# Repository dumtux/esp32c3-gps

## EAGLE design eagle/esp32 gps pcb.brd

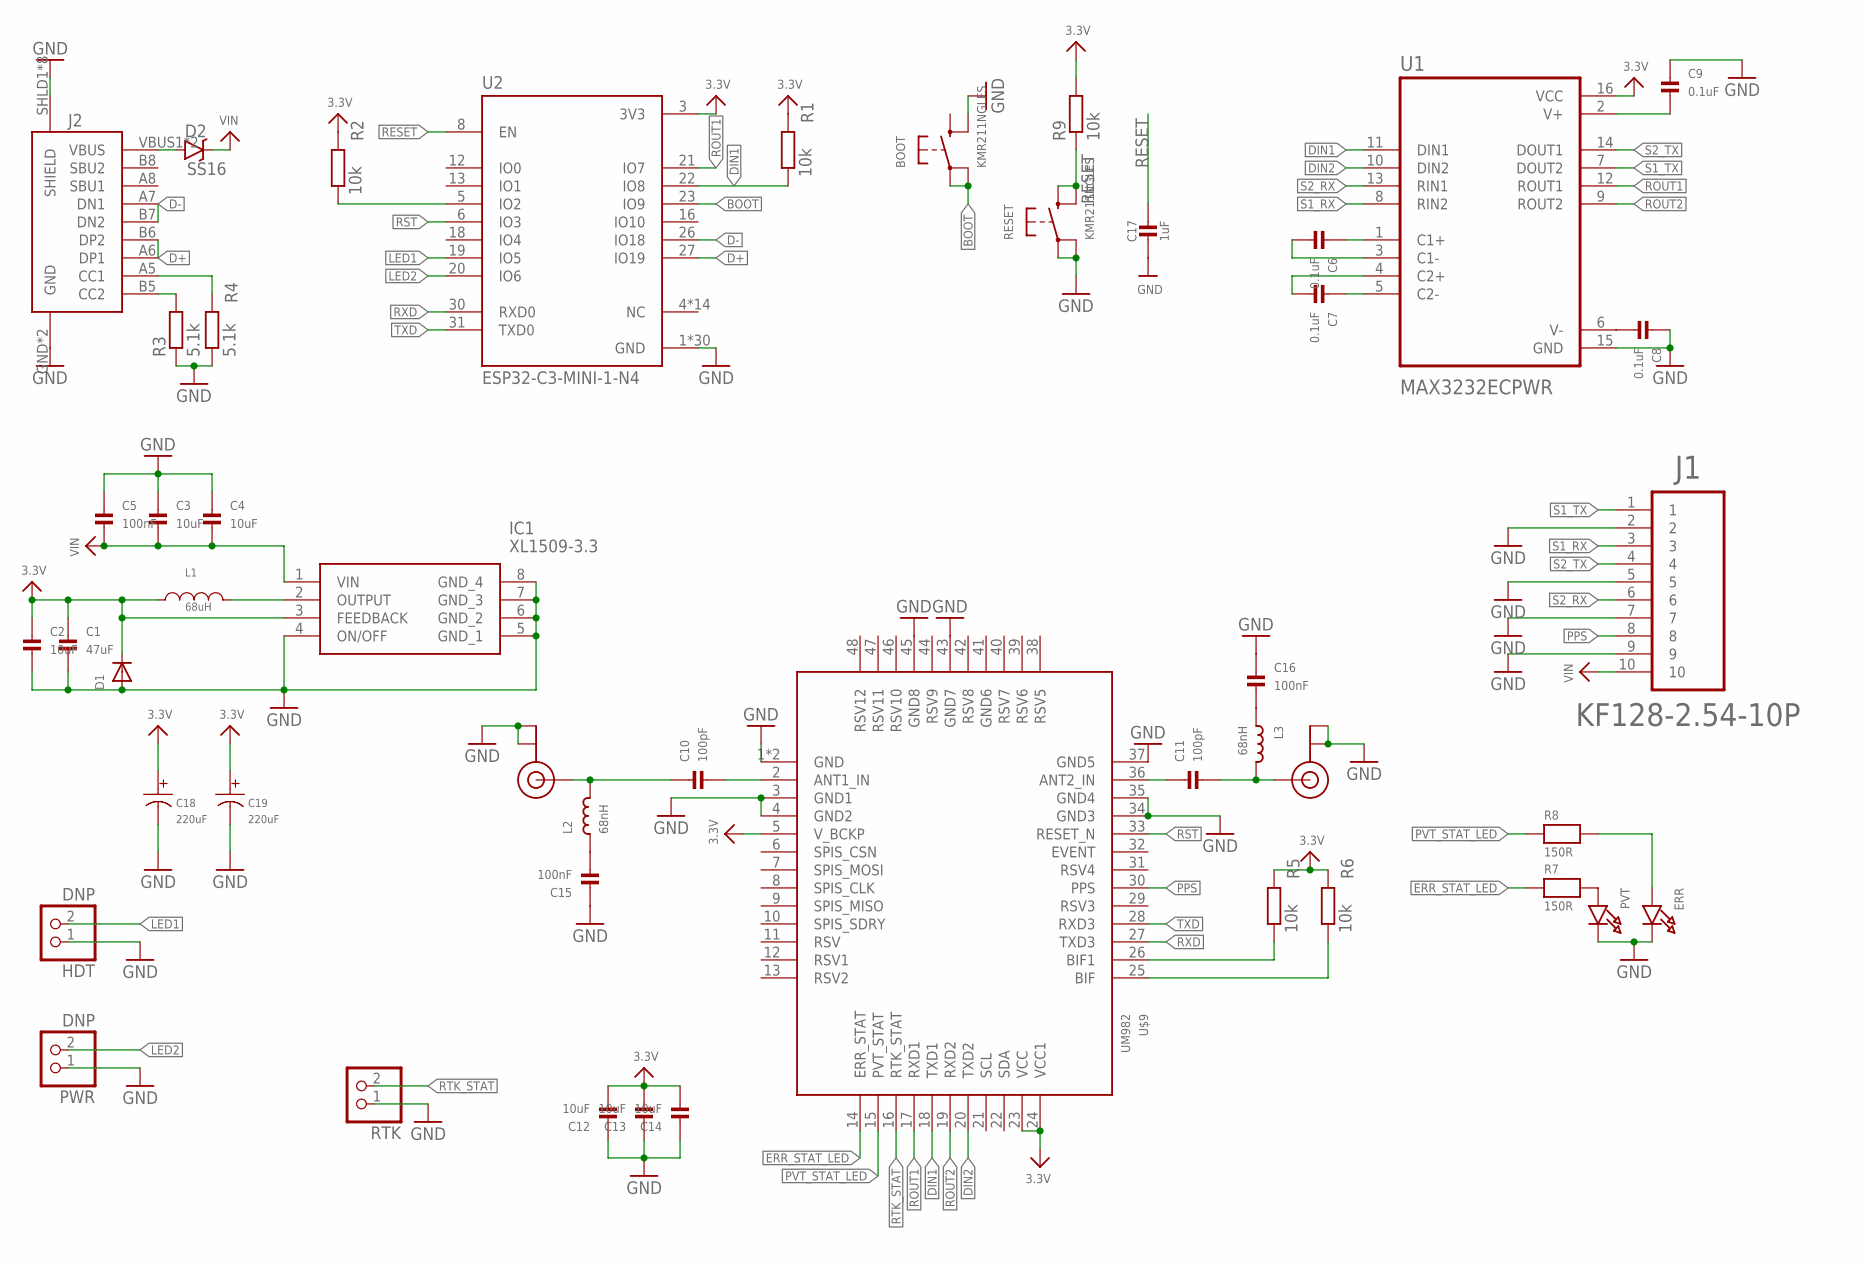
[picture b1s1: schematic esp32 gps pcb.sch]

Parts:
BOOT: KMR211NGLFS; BTN_KMR2_4.6X2.8
C1: 47uF; _0805
C2, C3, C4, C12, C13, C14: 10uF; _0603
C5, C15, C16: 100nF; _0603
C6, C7, C8, C9: 0.1uF; _0603
C10, C11: 100pF; _0603
C17: 1uF; _0603
C18, C19: 220uF; CAP-SMD_BD6.3-L6.6-W6.6-FD
D1: DIODESMA; SMADIODE
D2: SS16; SMA-DIODE
ERR: LED0603; CHIPLED_0603
HDT: DNP; 1X02_ROUND
IC1: XL1509-3.3; SOIC127P600X175-8N
J1: KF128-2.54-10P
J2: TYP-C16PIN2MD; USB-C-16P
L1: 68uH; IND-SMD_L6.0-W6.0
L2, L3: 68nH; _0603
PRI: KH-IPEX-K501-29; U.FL
PVT: LED0603; CHIPLED_0603
PWR: DNP; 1X02_ROUND
R1, R2, R5, R6: 10k; R0402
R3, R4: 5.1k; R0402
R7, R8: 150R; _0603
R9: 10k; R0603
RESET: KMR211NGLFS; BTN_KMR2_4.6X2.8
RTK: HEADER-1X2ROUND; 1X02_ROUND
SEC: KH-IPEX-K501-29; U.FL
U1: MAX3232ECPWR; SOP65P640X120-16N
U2: ESP32-C3-MINI-1-N4; XCVR_ESP32-C3-MINI-1-N4
U$9: UM982

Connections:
3.3V: C1.1, C2.1, C12.2, C13.2, C14.2, C18.1, C19.1, D1.C, IC1.3 (FEEDBACK), L1.1, R1.2, R2.2, R5.2, R6.2, R9.2, U1.16 (VCC), U2.3 (3V3), U$9.5 (V_BCKP), U$9.23 (VCC), U$9.24 (VCC1)
BOOT: BOOT.A, BOOT.A' (P1), U2.23 (IO9)
D+: J2.A6 (DP1), J2.B6 (DP2), U2.27 (IO19)
D-: J2.A7 (DN1), J2.B7 (DN2), U2.26 (IO18)
DIN1: R1.1, U1.11 (DIN1), U2.22 (IO8), U$9.18 (TXD1)
DIN2: U1.10 (DIN2), U$9.20 (TXD2)
ERR_STAT_LED: R7.1, U$9.14 (ERR_STAT)
GND: BOOT.B' (S1), C1.2, C2.2, C3.1, C4.1, C5.1, C8.1, C9.1, C12.1, C13.1, C14.1, C15.1, C16.1, C17.2, C18.2, C19.2, D1.A, ERR.C, HDT.1, IC1.4 (ON/OFF), IC1.5 (GND_1), IC1.6 (GND_2), IC1.7 (GND_3), IC1.8 (GND_4), J1.2, J1.5, J1.7, J1.9, J2.GND, J2.GND2 (GND), J2.SHLD1 (SHIELD), J2.SHLD2 (SHIELD), J2.SHLD3 (SHIELD), J2.SHLD4 (SHIELD), J2.SHLD5 (SHIELD), J2.SHLD6 (SHIELD), J2.SHLD7 (SHIELD), J2.SHLD8 (SHIELD), PRI.1 (GND), PRI.2 (GND), PVT.C, PWR.1, R3.1, R4.1, RESET.A, RESET.A' (P1), RTK.1, SEC.1 (GND), SEC.2 (GND), U1.15 (GND), U2.1 (GND), U2.2 (GND), U2.11 (GND), U2.14 (GND), U2.36 (GND), U2.37 (GND), U2.38 (GND), U2.39 (GND), U2.40 (GND), U2.41 (GND), U2.42 (GND), U2.43 (GND), U2.44 (GND), U2.45 (GND), U2.46 (GND), U2.47 (GND), U2.48 (GND), U2.49_1 (GND), U2.49_2 (GND), U2.49_3 (GND), U2.49_4 (GND), U2.49_5 (GND), U2.49_6 (GND), U2.49_7 (GND), U2.49_8 (GND), U2.49_9 (GND), U2.50 (GND), U2.51 (GND), U2.52 (GND), U2.53 (GND), U$9.1 (GND), U$9.3 (GND1), U$9.4 (GND2), U$9.34 (GND3), U$9.35 (GND4), U$9.37 (GND5), U$9.43 (GND7), U$9.45 (GND8), U$9.P$1 (GND)
LED1: HDT.2, U2.19 (IO5)
LED2: PWR.2, U2.20 (IO6)
unnamed: C6.1, U1.1 (C1+)
unnamed: C8.2, U1.6 (V-)
unnamed: C10.1, L2.2, PRI.3 (SIGNAL)
unnamed: C6.2, U1.3 (C1-)
unnamed: C9.2, U1.2 (V+)
unnamed: C10.2, U$9.2 (ANT1_IN)
unnamed: C7.1, U1.5 (C2-)
unnamed: C7.2, U1.4 (C2+)
unnamed: C11.1, U$9.36 (ANT2_IN)
unnamed: R5.1, U$9.26 (BIF1)
unnamed: J2.B5 (CC2), R3.2
unnamed: J2.A5 (CC1), R4.2
unnamed: D2.A, J2.VBUS1 (VBUS), J2.VBUS2 (VBUS)
unnamed: IC1.2 (OUTPUT), L1.2
unnamed: R2.1, U2.5 (IO2)
unnamed: R6.1, U$9.25 (BIF)
unnamed: C11.2, L3.2, SEC.3 (SIGNAL)
unnamed: C15.2, L2.1
unnamed: PVT.A, R7.2
unnamed: C16.2, L3.1
unnamed: ERR.A, R8.2
PPS: J1.8, U$9.30 (PPS)
PVT_STAT_LED: R8.1, U$9.15 (PVT_STAT)
RESET: C17.1, R9.1, RESET.B (S), RESET.B' (S1), U2.8 (EN)
ROUT1: U1.12 (ROUT1), U2.21 (IO7), U$9.17 (RXD1)
ROUT2: U1.9 (ROUT2), U$9.19 (RXD2)
RST: U2.6 (IO3), U$9.33 (RESET_N)
RTK_STAT: RTK.2, U$9.16 (RTK_STAT)
RXD: U2.30 (RXD0), U$9.27 (TXD3)
S1_RX: J1.3, U1.8 (RIN2)
S1_TX: J1.1, U1.7 (DOUT2)
S2_RX: J1.6, U1.13 (RIN1)
S2_TX: J1.4, U1.14 (DOUT1)
TXD: U2.31 (TXD0), U$9.28 (RXD3)
VIN: C3.2, C4.2, C5.2, D2.C, IC1.1 (VIN), J1.10

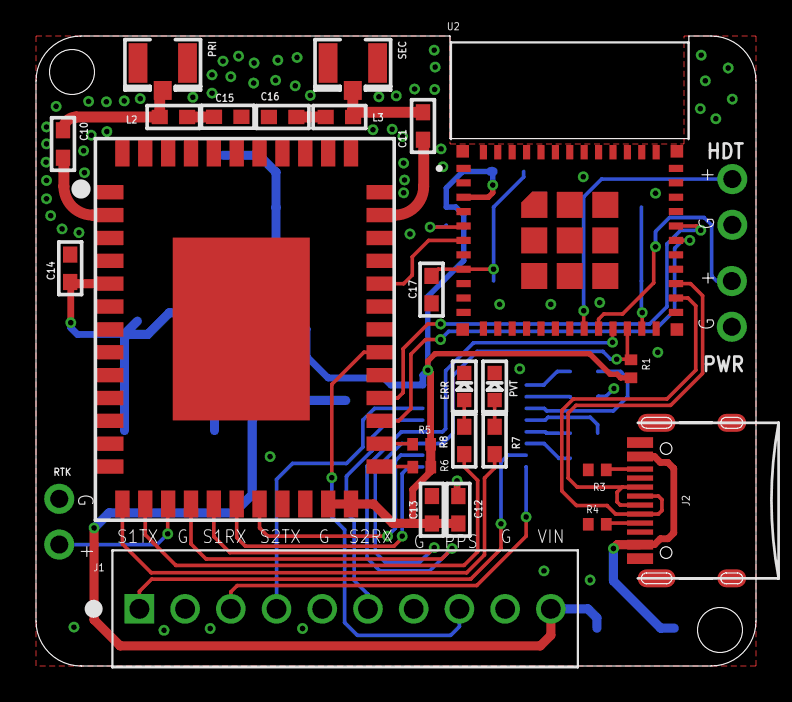
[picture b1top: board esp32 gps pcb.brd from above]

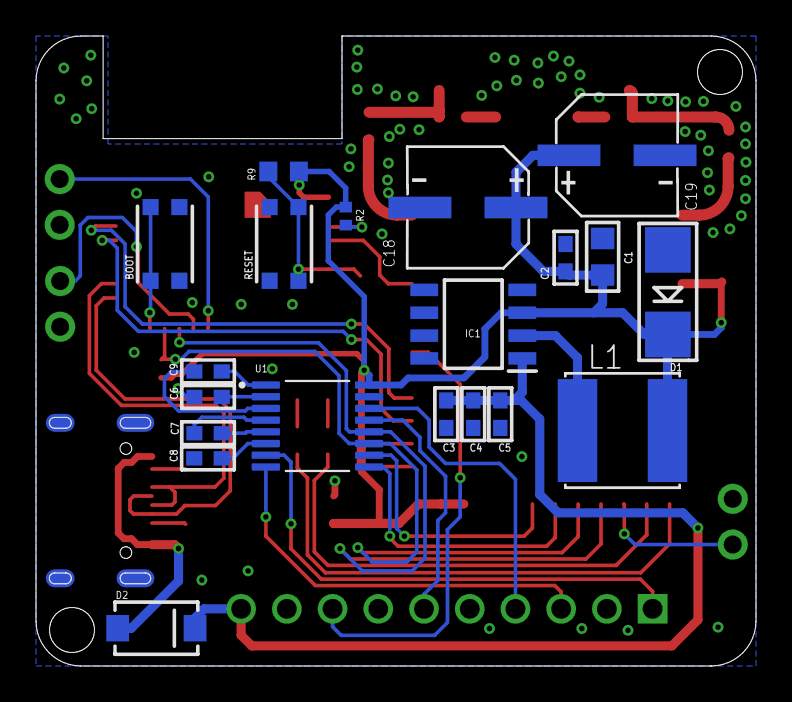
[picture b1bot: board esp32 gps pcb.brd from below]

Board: 2 copper layers, 40.0 x 35.0 mm, 48 parts (20 on the bottom side), 45 nets.

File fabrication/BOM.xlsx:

Qty | Value | Device | Package | Parts | Description | Manufacturer Part Number | LCSC Part Number
1 | SS16 | DIODESMA | SMADIODE | D1 | Diode
1 | Do not place | HEADER-1X2ROUND | 1X02_ROUND | RTK | PIN HEADER
2 | RED | LED0603 | CHIPLED_0603 | ERR, PVT | LED
1 | 68uH | PNLS6045-680 | PNLS6045-680 | L1 | 1.6A 68uH ±20% 330mΩ SMD,6x6x4.5mm Power Inductors ROHS | PNLS6045-680 | C2849542
1 |  | TYP-C16PIN2MD | USB-C-16P | J2 | Check availability
4 | 0.1uF | CAP_CERAMIC_0603 | _0603 | C6, C7, C8, C9 | Ceramic Capacitors
3 | 100nF | CAP_CERAMIC_0603 | _0603 | C5, C15, C16 | Ceramic Capacitors
2 | 100pF | CAP_CERAMIC_0603 | _0603 | C10, C11 | Ceramic Capacitors
4 | 10k | R-EU_R0402 | R0402 | R1, R2, R5, R6 | RESISTOR, European symbol
1 | 10k | R-EU_R0603 | R0603 | R9 | RESISTOR, European symbol
6 | 10uF | CAP_CERAMIC_0603 | _0603 | C2, C3, C4, C12, C13, C14 | Ceramic Capacitors
2 | 150R | RESISTOR_0603 | _0603 | R7, R8 | Resistors
1 | 1uF | CAP_CERAMIC_0603 | _0603 | C17 | Ceramic Capacitors
1 | 47uF | CAP_CERAMIC_0805 | _0805 | C1 | Ceramic Capacitors
2 | 220uF | CAP_Electrolytic | SMD,D6.3xL5.4mm | C18, C19 | Aluminum Electrolytic Capacitors | RVT1A221M0605 | C72494
2 | 5.1k | R-EU_R0402 | R0402 | R3, R4 | RESISTOR, European symbol
2 | 68nH | INDUCTOR_0603 | _0603 | L2, L3 | Inductors
2 | DNP | HEADER-1X2ROUND | 1X02_ROUND | HDT, PWR | PIN HEADER
1 | ESP32-C3-MINI-1-N4 | ESP32-C3-MINI-1-N4 | XCVR_ESP32-C3-MINI-1-N4 | U2 | Check availability
1 | KF128-2.54-10P | KF128-2.54-10P | KF128-2.54-10P | J1 | TERM BLOCK 10POS SIDE ENT 2.54MM
2 | KH-IPEX-K501-29 | U.FL | U.FL | PRI, SEC | U.FL Antenna Connector
2 | KMR211NGLFS | SWITCH_TACT_SMT4.6X2.8 | BTN_KMR2_4.6X2.8 | BOOT, RESET | SMT Tact Switches
1 | MAX3232ECPWR | MAX3232ECPWR | SOP65P640X120-16N | U1
1 | SS16 | DIODE-SCHOTTKY-B340A | SMA-DIODE | D2 | Schottky diodes in SFE's production catalog
1 | UM982 | UM982 | UM982 | U$9
1 | XL1509-3.3 | XL1509-3.3 | SOIC127P600X175-8N | IC1 | gh

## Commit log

2023-02-17 initial commit.
2023-09-07 update on 20230907

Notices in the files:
parts and their libraries:
SparkFun-DiscreteSemi: Licensing: Creative Commons ShareAlike 4.0 International - https://creativecommons.org/licenses/by-sa/4.0
microbuilder: This work is placed in the public domain, and may be freely used for commercial and non-commercial work with the following conditions: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
